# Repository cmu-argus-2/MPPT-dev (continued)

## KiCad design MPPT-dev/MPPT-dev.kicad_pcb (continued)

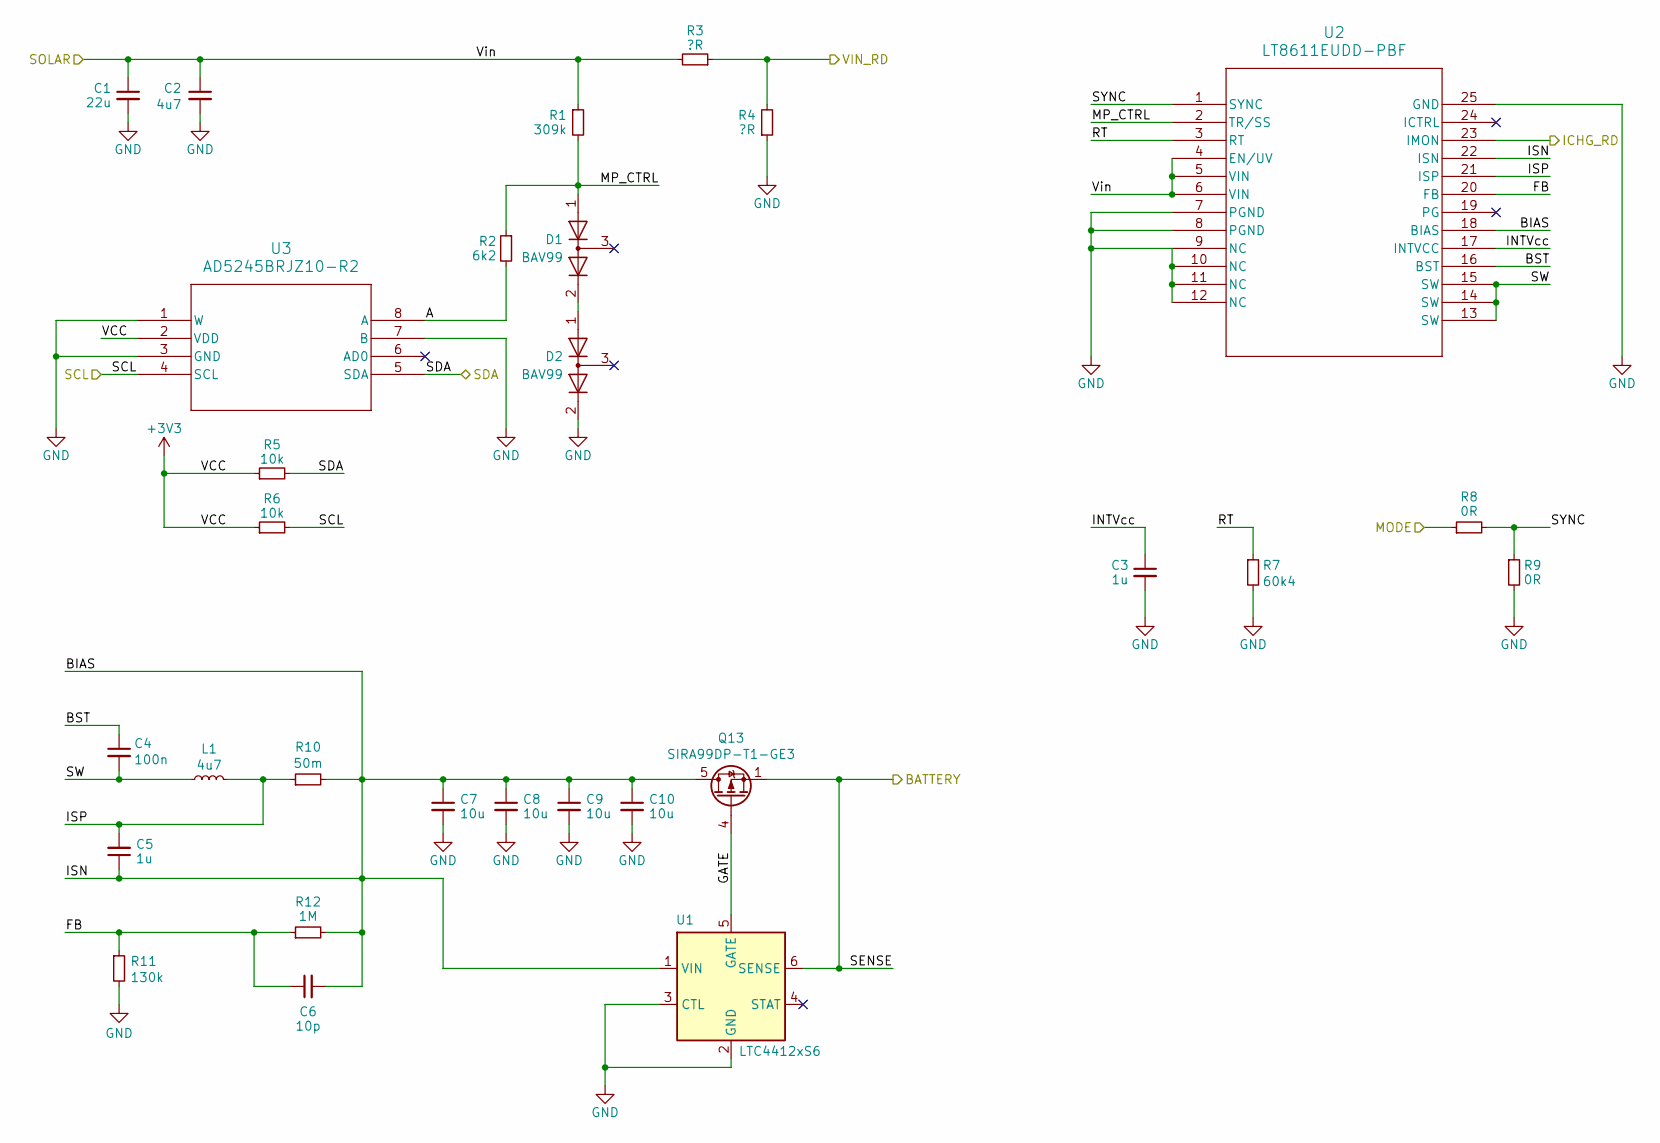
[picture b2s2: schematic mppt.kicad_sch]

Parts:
C1: 22u; C_0603_1608Metric
C2: 4u7; C_0603_1608Metric
C3, C5: 1u; C_0603_1608Metric
C4: 100n; C_0603_1608Metric
C6: 10p; C_0603_1608Metric
C7, C8, C9, C10: 10u; C_0603_1608Metric
D1, D2: BAV99; SOT-23
L1: 4u7; IND_03-4R7-R_EAT
Q13: SIRA99DP-T1-GE3; PowerPAK_SO-8_Single; MPN C3289459
R1: 309k; R_0603_1608Metric
R2: 6k2; R_0603_1608Metric
R3, R4: ?R; R_0603_1608Metric
R5, R6: 10k; R_0603_1608Metric
R7: 60k4; R_0603_1608Metric
R8, R9: 0R; R_0603_1608Metric
R10: 50m; R_0603_1608Metric
R11: 130k; R_0603_1608Metric
R12: 1M; R_0603_1608Metric
U1: LTC4412xS6; TSOT-23-6
U2: LT8611EUDD-PBF; QFN-24_UDD_LTI
U3: AD5245BRJZ10-R2; RJ_8_ADI

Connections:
+3V3: R5.1, R6.1, U3.2 (VDD); also elsewhere on the board
/BATTERY: Q13.1 (S), Q13.2 (S), Q13.3 (S), U1.6 (SENSE); also elsewhere on the board
/D_VSOLAR1: C1.1, C2.1, R1.1, R3.2, U2.4 (EN/UV), U2.5 (VIN), U2.6 (VIN); also elsewhere on the board
/ICHG_RD: U2.23 (IMON); also elsewhere on the board
/MODE: R8.1; also elsewhere on the board
/MPPT/A: R2.2, U3.8 (A)
/MPPT/BIAS: C5.1, C6.2, C7.1, C8.1, C9.1, C10.1, Q13.5 (D), R10.2, R12.2, U1.1 (VIN), U2.18 (BIAS), U2.22 (ISN)
/MPPT/BST: C4.1, U2.16 (BST)
/MPPT/FB: C6.1, R11.1, R12.1, U2.20 (FB)
/MPPT/GATE: Q13.4 (G), U1.5 (GATE)
/MPPT/INTVcc: C3.1, U2.17 (INTVCC)
/MPPT/ISP: C5.2, L1.2, R10.1, U2.21 (ISP)
/MPPT/MP_CTRL: D1.1 (K), R1.2, R2.1, U2.2 (TR/SS)
/MPPT/RT: R7.1, U2.3 (RT)
/MPPT/SW: C4.2, L1.1, U2.13 (SW), U2.14 (SW), U2.15 (SW)
/MPPT/SYNC: R8.2, R9.1, U2.1 (SYNC)
/SCL: R6.2, U3.4 (SCL); also elsewhere on the board
/SDA: R5.2, U3.5 (SDA); also elsewhere on the board
/VIN_RD: R3.1, R4.2; also elsewhere on the board
GND: C1.2, C2.2, C3.2, C7.2, C8.2, C9.2, C10.2, D2.2 (A), R4.1, R7.2, R9.2, R11.2, U1.2 (GND), U1.3 (CTL), U2.7 (PGND), U2.8 (PGND), U2.9 (NC), U2.10 (NC), U2.11 (NC), U2.12 (NC), U2.25 (GND), U3.1 (W), U3.3 (GND), U3.7 (B); also elsewhere on the board
unnamed: D1.2 (A), D2.1 (K)

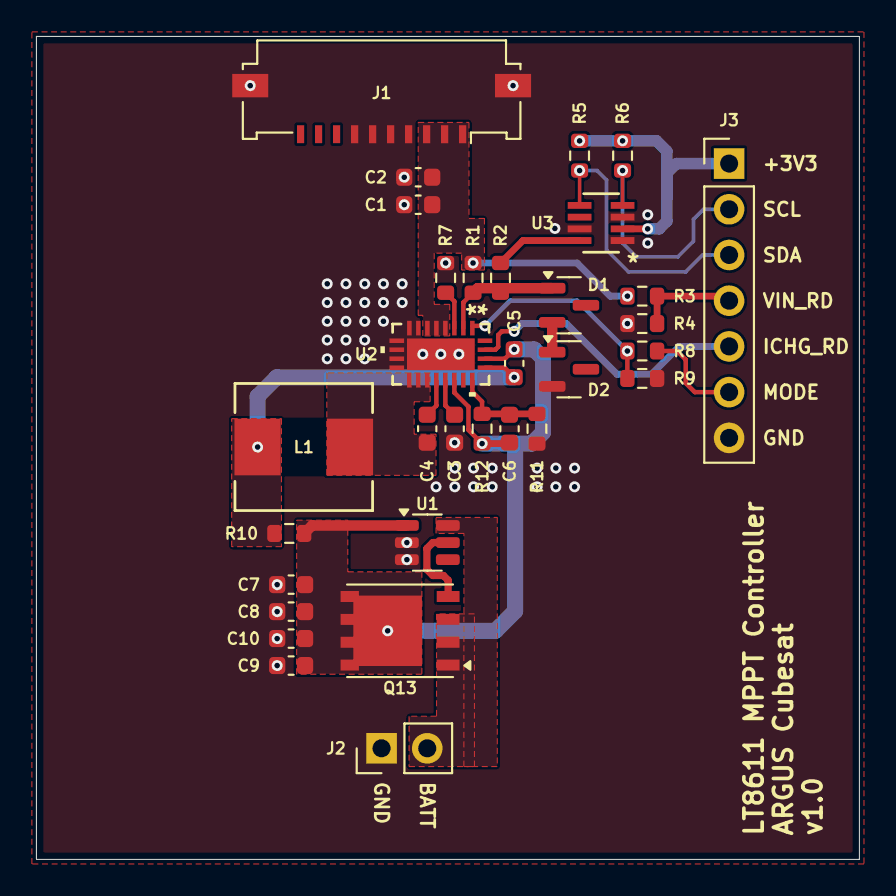
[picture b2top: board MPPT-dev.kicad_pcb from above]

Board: 2 copper layers, 45.7 x 45.7 mm, 32 parts (0 on the bottom side), 21 nets.

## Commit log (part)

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2025-09-03 basic mppt
2025-09-03 updated local lib path
2025-09-04 usb connector
2025-09-04 missing files
2025-09-05 initial layout
2025-09-07 1 mppt layout
2025-09-29 Add .gitignore
2025-09-29 Board review
2025-11-26 Stash
